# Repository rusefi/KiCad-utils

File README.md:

# KiCad-utils
A collection of tools for command line KiCad file manipulation.

A suite of command line tools designed for KiCad command line manipulation including PCB merge.

It could be that a number of bycicles were reinvented here and Python is the way to go with KiCad?

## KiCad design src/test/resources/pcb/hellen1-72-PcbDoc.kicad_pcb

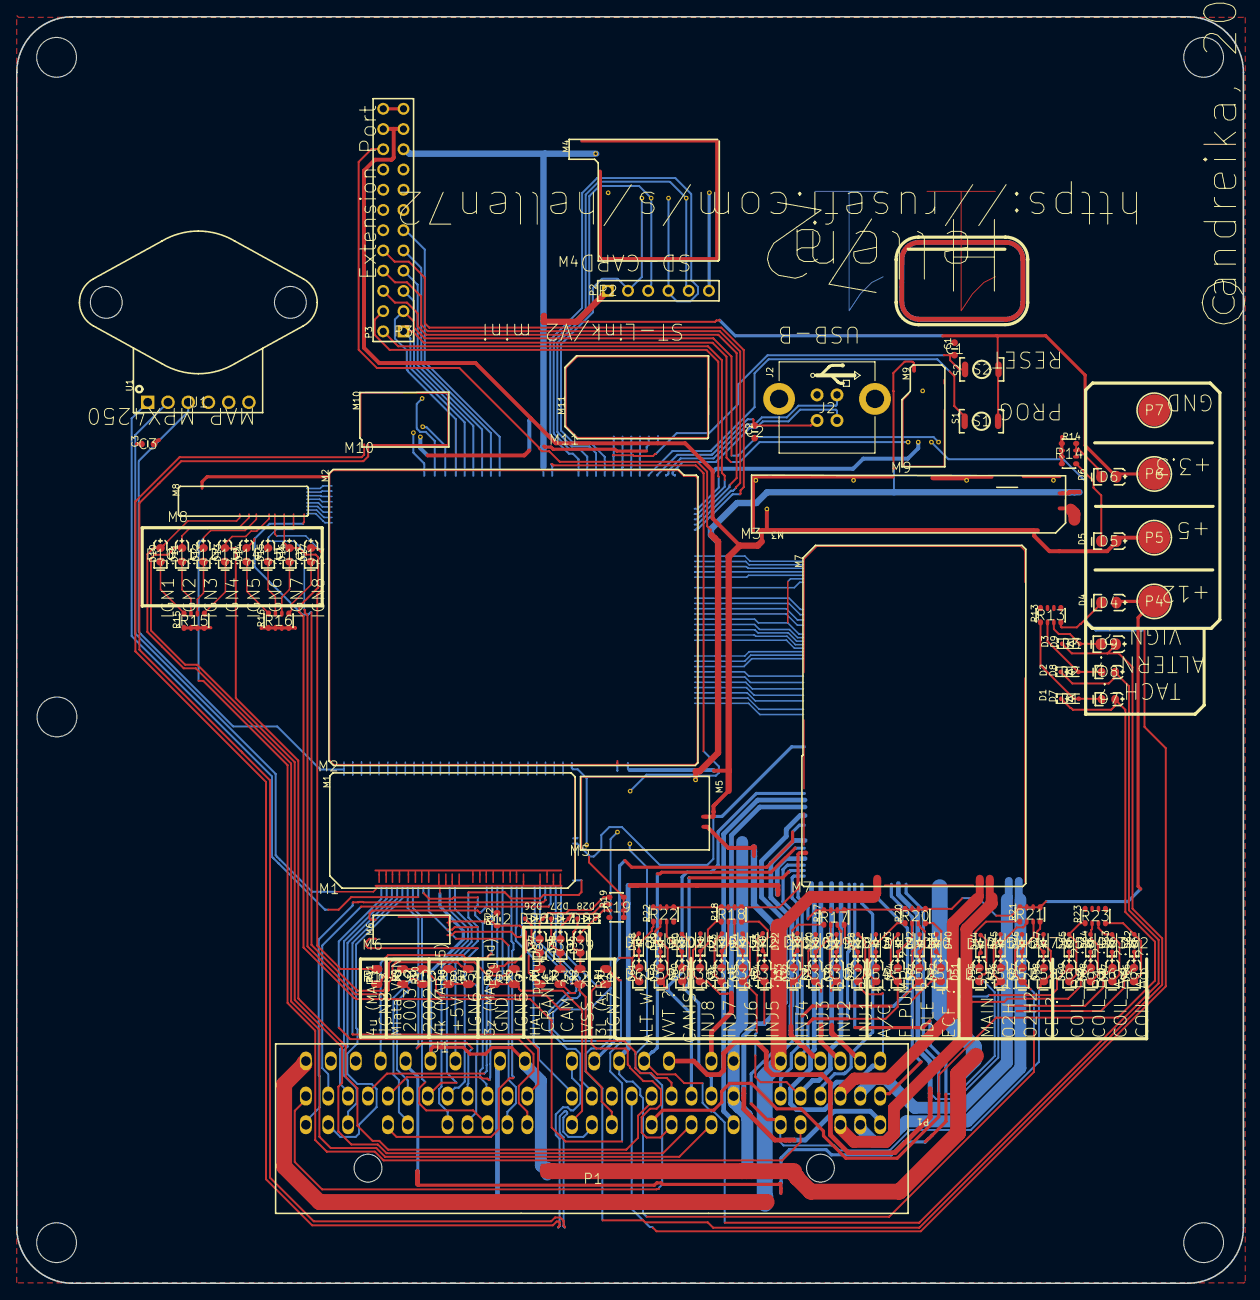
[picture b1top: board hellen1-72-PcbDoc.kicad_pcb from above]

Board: 2 copper layers, 154.0 x 159.0 mm, 118 parts (0 on the bottom side), 204 nets.

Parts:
C1: C1; C0603
C2: C2; C0603
C3: C3; C0603
D1: D1; SOD-323
D2: D2; SOD-323
D3: D3; SOD-323
D4: D4; LED-0805
D5: D5; LED-0805
D6: D6; LED-0805
D7: D7; LED-0603
D8: D8; LED-0603
D9: D9; LED-0805
D10: D10; LED-0603
D11: D11; LED-0603
D12: D12; LED-0603
D13: D13; LED-0603
D14: D14; LED-0603
D15: D15; LED-0603
D16: D16; LED-0603
D17: D17; LED-0603
D18: D18; SOD-323
D19: D19; SOD-323
D20: D20; SOD-323
D21: D21; SOD-323
D22: D22; SOD-323
D23: D23; SOD-323
D24: D24; SOD-323
D25: D25; SOD-323
D26: D26; SOD-323
D27: D27; SOD-323
D28: D28; SOD-323
D29: D29; LED-0603
D30: D30; LED-0603
D31: D31; LED-0603
D32: D32; LED-0603
D33: D33; LED-0603
D34: D34; LED-0603
D35: D35; LED-0603
D36: D36; LED-0603
D37: D37; LED-0603
D38: D38; LED-0603
D39: D39; LED-0603
D40: D40; SOD-323
D41: D41; SOD-323
D42: D42; SOD-323
D43: D43; SOD-323
D44: D44; SOD-323
D45: D45; SOD-323
D46: D46; SOD-323
D47: D47; SOD-323
D48: D48; SOD-323
D49: D49; SOD-323
D50: D50; SOD-323
D51: D51; LED-0603
D52: D52; LED-0603
D53: D53; LED-0603
D54: D54; LED-0603
D55: D55; LED-0603
D56: D56; LED-0603
D57: D57; LED-0603
D58: D58; LED-0603
D59: D59; LED-0603
D60: D60; LED-0603
D61: D61; LED-0603
D62: D62; SOD-323
D63: D63; SOD-323
D64: D64; SOD-323
D65: D65; SOD-323
D66: D66; LED-0603
D67: D67; LED-0603
D68: D68; LED-0603
D69: D69; LED-0603
J1: J1; NET-TIE
J2: J2; CONN-USB-B-VERTICAL
M1: M1; MOD_Hellen_Input
M2: M2; MOD_Hellen_MCU
M3: M3; MOD_Hellen_POWER_5
M4: M4; MOD_HELLEN_SD
M5: M5; MOD_Hellen_POWER_12
M6: M6; MOD_Hellen_Knock
M7: M7; MOD_Hellen_OUTPUT
M8: M8; MOD_Hellen_IGN8
M9: M9; MOD_Hellen_LIN
M10: M10; MOD_Hellen_CAN
M11: M11; MOD_HELLEN_STLINK
P1: P1; CONN-TE-72-PIN
P2: P2; HDR1X6
P3: P3; HDR2X12
P4: P4; PAD-SMD-4.0
P5: P5; PAD-SMD-4.0
P6: P6; PAD-SMD-4.0
P7: P7; PAD-SMD-4.0
R1: R1; R0805
R2: R2; R0805
R3: R3; R0805
R4: R4; R0805
R5: R5; R0805
R6: R6; R0805
R7: R7; R0805
R8: R8; R0805
R9: R9; R0805
R10: R10; R0805
R11: R11; R0805
R12: R12; R0603
R13: R13; R0603_x4
R14: R14; R0603_x4
R15: R15; R0603_x4
R16: R16; R0603_x4
R17: R17; R0603_x4
R18: R18; R0603_x4
R19: R19; R0603_x4
R20: R20; R0603_x4
R21: R21; R0603_x4
R22: R22; R0603_x4
R23: R23; R0603_x4
S1: S1; BUTTON-SKRK
S2: S2; BUTTON-SKRK
U1: U1; MPX4250AP

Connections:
AC: M2.E9, M7.W37
AC_PRESS: M1.N10, M2.S24
AFR: M1.N26, M2.S8
ALTERN: M2.E19, M7.W28
ALT_WARN: M2.E7, M7.W39
BOOT0: M2.N26, S1.1
BRAKE: M1.N6, M2.S28
CAM: M1.N19, M2.S15
CAM_PULLUP: D27.2, D38.2, R3.2
CANIST: M2.E21, M7.W26
CAN_N: M10.S1, P1.3X
CAN_P: M10.S2, P1.3W
CAN_RX: M2.N2, M10.V6
CAN_TX: M2.N3, M10.V5
CAN_VIO: M2.N1, M10.V2
CE: M2.E22, M7.W25
CLT: M1.N16, M2.S18
CLUTCH: M1.N8, M2.S26
COIL_A1: M2.E14, M7.W33
COIL_A2: M2.E15, M7.W32
COIL_B1: M2.E16, M7.W31
COIL_B2: M2.E17, M7.W30
CRANK: M1.N21, M2.S13
CRANK_PULLUP: D26.2, D37.2, R4.2
ECF: M2.E28, M7.W21
EGR: M1.N11, M2.S23
EXT_IO1: M2.N6, P3.5
EXT_IO2: M2.N7, P3.7
EXT_IO3: M2.N8, P3.9
EXT_IO4: M2.N9, P3.11
EXT_SPI_CS1: M2.E4, P3.8
EXT_SPI_CS2: M2.E5, P3.10
EXT_SPI_MISO: M2.E2, P3.2
EXT_SPI_MOSI: M2.E3, P3.6
EXT_SPI_SCK: M2.E1, P3.4
FTP_PPS: M1.N5, M2.S29
FUEL_LEVEL: M1.N24, M2.S10
GND: C1.2, C2.1, J1.1, J2.4, M1.E1, M1.E5, M2.S2, M3.E1, M3.V1, M3.V2, M3.V3, M3.V4, M4.G, M4.V2, M4.V3, M5.S1, M7.G, M7.S3, M8.G, M9.E1, M9.S1, M10.E1, M11.G, P1.3A, P1.3B, P1.4A, P2.6, P3.23, P3.24, P7.1, R13.5, R13.6, R13.7, R13.8, R14.5, R14.6, R14.7, R14.8, R15.5, R15.6, R15.7, R15.8, R16.5, R16.6, R16.7, R16.8, R23.5, R23.6, R23.7, R23.8
GNDA: C3.2, J1.2, M1.J2, M1.J11, M1.J12, M1.J13, M1.J14, M1.J22, M1.J23, M1.J25, M1.J26, M1.N2, M2.S32, M6.E1, P1.4O, R6.2, R12.1, U1.2
IAT: M1.N15, M2.S19
IDLE: M2.E18, M7.W29, M7.W35
IGN1: M2.W1, M8.E8
IGN2: M2.W2, M8.E7
IGN3: M2.W3, M8.E6
IGN4: M2.W4, M8.E5
IGN5: M2.W5, M8.E4
IGN6: M2.W6, M8.E3
IGN7: M2.W7, M8.E2
IGN8: M2.W8, M8.E1
INJ1: M2.E25, M7.W24
INJ2: M2.E26, M7.W23
INJ3: M2.E29, M7.W20
INJ4: M2.E30, M7.W19
INJ5: M2.E31, M7.W18
INJ6: M2.E32, M7.W17
INJ7: M2.E33, M7.W16
INJ8: M2.E34, M7.W15
IN_AC_PRESS: M1.S17, P1.4F
IN_AFR: M1.S1, P1.3L, R1.1
IN_BRAKE: M1.S23, P1.4B
IN_CAM: M1.S5, P1.3V, R3.1
IN_CLT: M1.S15, P1.4P
IN_CLUTCH: M1.S20, P1.4I
IN_CRANK: M1.S8, P1.3Y, R4.1
IN_EGR: M1.S22, P1.4AE
IN_FTP_PPS: M1.S24, P1.4AB
IN_FUEL_LEVEL: M1.S3, P1.4AD
IN_IAT: M1.S16, P1.4N
IN_KNOCK: M1.S7, M6.E3
IN_KNOCK_RAW: M6.W1, P1.4M
IN_MAF: M1.S11, P1.4X, R12.2
IN_MAP2: M1.S12, P1.4U, R11.1
IN_MAP3: M1.S19, U1.1
IN_NEUTRAL: M1.S18, P1.4H
IN_O2S: M1.S9, P1.4W
IN_O2S2: M1.S25, P1.4AA
IN_SENS2: M1.S2, P1.3K
IN_SENS4: M1.S4, P1.4AH
IN_STEERING: M1.S26, P1.4C
IN_TPS: M1.S10, P1.4V
IN_VIGN: D3.1, D9.1, M5.V3, R9.2, R10.2
IN_VSS: M1.S6, P1.3T, R2.1
IN_VTCS: M1.S21, P1.4J
KNOCK: M1.N22, M2.S12
LIN: M9.V4, P1.3Q
MAF: M1.N14, M2.S20
MAIN: M2.E6, M7.W40
MAP2: M1.N13, M2.S21
MAP3: M1.N12, M2.S22
NEUTRAL: M1.N9, M2.S25
NetD1_2: D1.2, D7.2, R13.1
NetD2_2: D2.2, D8.2, R13.2
NetD3_2: D3.2, D9.2, R13.3
NetD4_2: D4.2, R13.4
NetD5_2: D5.2, R14.1
NetD6_2: D6.2, R14.2, R14.3, R14.4
NetD10_2: D10.2, R15.4
NetD11_2: D11.2, R15.3
NetD12_2: D12.2, R15.2
NetD13_2: D13.2, R15.1
NetD14_2: D14.2, R16.4
NetD15_2: D15.2, R16.3
NetD16_2: D16.2, R16.2
NetD17_2: D17.2, R16.1
NetD18_1: D18.1, D29.1, R17.4
NetD19_1: D19.1, D30.1, R17.3
NetD20_1: D20.1, D31.1, R17.2
NetD21_1: D21.1, D32.1, R17.1
NetD22_1: D22.1, D33.1, R18.4
NetD23_1: D23.1, D34.1, R18.3
NetD24_1: D24.1, D35.1, R18.2
NetD25_1: D25.1, D36.1, R18.1
NetD26_1: D26.1, D37.1, R19.1
NetD27_1: D27.1, D38.1, R19.2
NetD28_1: D28.1, D39.1, R19.3
NetD40_1: D40.1, D51.1, R20.4
NetD41_1: D41.1, D52.1, R20.3
NetD42_1: D42.1, D53.1, R20.2
NetD43_1: D43.1, D54.1, R20.1
NetD44_1: D44.1, D55.1, R21.1
NetD45_1: D45.1, D56.1, R21.2
NetD46_1: D46.1, D57.1, R21.3
NetD47_1: D47.1, D58.1, R21.4
NetD48_1: D48.1, D61.1, R22.1
NetD49_1: D49.1, D59.1, R22.2
NetD50_1: D50.1, D60.1, R22.3
NetD62_2: D62.2, D66.2, R23.4
NetD63_2: D63.2, D67.2, R23.3
NetD64_2: D64.2, D68.2, R23.2
NetD65_2: D65.2, D69.2, R23.1
NetP1_3Z: P1.3Z, R5.1, R6.1
NetP1_4K: P1.4K, R7.1, R8.1
NetP1_4S: P1.4S, R9.1
NetP1_4T: P1.4T, R10.1
O2H: M2.E8, M7.W38
O2H2: M2.E12, M7.W34
O2S: M1.N18, M2.S16
O2S2: M1.N4, M2.S30
OUT_AC: D43.2, D54.2, M7.S12, P1.2K
OUT_ALTERN: D2.1, D8.1, M7.W6, P1.3M
OUT_ALT_WARN: D48.2, D61.2, M7.W9, P1.3U
OUT_CANIST: D50.2, D60.2, M7.W2, P1.3E
OUT_CE: D47.2, D58.2, M7.W3, P1.2R
OUT_COIL_A1: D62.1, D66.1, M7.S1, P1.2F
OUT_COIL_A2: D63.1, D67.1, M7.S2, P1.2E
OUT_COIL_B1: D64.1, D68.1, M7.S4, P1.2I
OUT_COIL_B2: D65.1, D69.1, M7.S5, P1.2H
OUT_ECF: D40.2, D51.2, M7.S8, P1.2B
OUT_IDLE: D41.2, D52.2, M7.S10, M7.W1, P1.2Q
OUT_IGN1: D10.1, M8.S8, P1.3F
OUT_IGN2: D11.1, M8.S7, P1.3I
OUT_IGN3: D12.1, M8.S6, P1.2O
OUT_IGN4: D13.1, M8.S5, P1.3N
OUT_IGN5: D14.1, M8.S1, R5.2
OUT_IGN6: D15.1, M8.S2, R7.2
OUT_IGN7: D16.1, M8.S3, R1.2
OUT_IGN8: D17.1, M8.S4, R11.2
OUT_INJ1: D18.2, D29.2, M7.S18, P1.2A
OUT_INJ2: D19.2, D30.2, M7.S16, P1.2D
OUT_INJ3: D20.2, D31.2, M7.S17, P1.2G
OUT_INJ4: D21.2, D32.2, M7.W7, P1.2J
OUT_INJ5: D22.2, D33.2, M7.W10, P1.2C
OUT_INJ6: D23.2, D34.2, M7.S15, P1.2N
OUT_INJ7: D24.2, D35.2, M7.W12, P1.3C
OUT_INJ8: D25.2, D36.2, M7.W11, P1.3D
OUT_MAIN: D49.2, D59.2, M7.W13, P1.3H
OUT_O2H: D45.2, D56.2, M7.S7, P1.3J
OUT_O2H2: D46.2, D57.2, M7.W4, P1.3P
OUT_PUMP: D42.2, D53.2, M7.S14, P1.2M
OUT_TACH: D1.1, D7.1, M7.S6, P1.3O
OUT_VVT: D44.2, D55.2, M7.S13, P1.4R
PUMP: M2.E20, M7.W27
SD_CS: M2.N21, M4.V4, P2.2
SD_MISO: M2.N19, M4.V7, P2.5
SD_MOSI: M2.N20, M4.V5, P2.3
SD_SCK: M2.N18, M4.V6, P2.4
SENS2: M1.N25, M2.S9
SENS4: M1.N23, M2.S11
STEERING: M1.N3, M2.S31
SWCLK: M2.N23, M11.N5
SWDIO: M2.N24, M11.N4
SWO: M2.N25, M11.N3
TACH: M2.E27, M7.W22
TPS: M1.N17, M2.S17
UART_RX: M2.N5, M9.V2, P3.1
UART_TX: M2.N4, M9.V5, P3.3
USB_N: J2.2, M2.N29
USB_P: J2.3, M2.N28
V5: D5.1, M1.E2, M2.S1, M3.V6, M5.E1, M7.W14, M9.V3, M10.V1, M11.N1, P3.21, P3.22, P5.1, R19.5, R19.6, R19.7, R19.8
V5A: C3.1, M1.E6, M1.J1, M1.J3, M1.J4, M1.J5, M1.J6, M1.J7, M1.J8, M1.J9, M1.J10, M1.J15, M1.J16, M1.J17, M1.J18, M1.J19, M1.J20, M1.J21, M1.J24, M1.N1, M2.S33, M6.E2, P1.4L, R8.2, U1.3
V12: M3.V5, M5.V1, M9.N1, M9.V1, P3.20
V12P: D4.1, M7.W5, P4.1, R17.5, R17.6, R17.7, R17.8, R18.5, R18.6, R18.7, R18.8, R20.5, R20.6, R20.7, R20.8, R21.5, R21.6, R21.7, R21.8, R22.5, R22.6, R22.7, R22.8
V12_PERM: M5.V4, P1.4AG
V12_RAW: M5.E2, M7.S11, P1.2P, P1.4AF, P1.4D
V33: D6.1, M2.N14, M4.V1, M11.N2, P2.1, P3.19, P6.1, S1.2, S2.2
VBAT: M2.N15, M5.V2
VBUS: C2.2, J2.1, M2.N27
VIGN: M2.S7, M5.V5
VREF2: M1.S13, M6.W2
VSS: M1.N20, M2.S14
VSS_PULLUP: D28.2, D39.2, R2.2
VTCS: M1.N7, M2.S27
VVT: M2.E10, M7.W36
nReset: C1.1, M2.N22, M11.N6, S2.1

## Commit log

2021-01-02 hello world
2021-01-02 NetList
2021-01-02 progress
2021-01-02 TDD is amazing
2021-01-02 it's all about the...
2021-01-02 GHA is so cool
2021-01-02 fancy?
2021-01-02 fancy!
2021-01-02 more tests
2021-01-02 docs
2021-01-07 tests improvements
2021-01-07 idea
2021-01-07 hellen
2021-01-07 weird
2021-01-07 bugfix - tabs was not a whitespace
2021-01-07 bugfix - module reference
2021-01-07 pads not merged
2021-01-07 pads are now merged
2021-01-07 net names are not merged right
2021-01-09 extract constant
2021-01-09 test coverage for existing class
2021-01-09 removing some dead code
2021-01-09 refactoring: static is evil
2021-01-09 refactoring
2021-01-09 minor progress
2021-01-10 refactoring towards net merge fix
2021-01-10 making test smaller
2021-01-10 BUGFIX: smarter network merge
2021-01-10 BUGFIX: mix-up between name and type
2021-01-10 BUGFIX: merged nets to me included into overall board
